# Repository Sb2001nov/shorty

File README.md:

# **Shorty (Re-Programable Macro Board)**

### you can fetch setup guide and files📂 [here](https://sb2001nov.github.io/shorty/)

## **Components Hardware Required:**

1. Raspberry pi Pico ([here](https://datasheets.raspberrypi.com/pico/pico-datasheet.pdf))
1. Cherry MX Style Switch’s ([here](https://cdn.sparkfun.com/datasheets/Components/Switches/MX%20Series.pdf))
1. General Purpose led ([here](https://learn.adafruit.com/all-about-leds/what-is-an-led))
1. Our PCB (here)

## **Specifications For Shorty:**

Contains 9 re-programmable keys for your macro, keys are laid out in 3x3 matrix.

1. **Switch:** Key switch with fixation pins (1 pole), hot swappable (should contain same mount point as mentioned).
1. **Keycaps:** can be 3d printed using given model or can pe purchased online.

### **Note:**
Match keycap size before purchasing, supported keycaps are alphabetic caps.

1. **Size:** x = 93.47mm, y = 62.99 mm
1. **Mounting:** Keycap can be mounted using 5 2.1 mm mounting bits.
1. **Connection:** Micro-B USB.

## **Programing Specification:**

1. micro-python - supported firmware and installation guide is [here](https://projects.raspberrypi.org/en/projects/getting-started-with-the-pico/3).
1. circuit-python - supported native and recommended to use.
1. C/C++ - can be uploaded using Thonny ide.
1. QMK firmware - customizable firmware.

## **Circuit Symantec**

Each switch is connected to a 3.3-Volt power pin and the other pin is connected to a GPIO pin to receive the data from the switch(input).
It also contains an LED connected with a resistor which you can use to show the status of anything you desire like showing if the circuit is receiving voltage. 

Buttons are connected in such a way that each button has its own GPIO pin, **why?**
</br>
Because it contains only 9 switches and it would be useless to reduce the number of pin because it will increase the complexity on the connection and increase the number of components used, leading to the code complexity.

*Complete information about RP2040 can be found [here*](https://datasheets.raspberrypi.com/pico/pico-datasheet.pdf)*

## **PCB Symantec**

All the details about PCB can be found on the GitHub, just open the PCB folder in KiCad.

PCB can be printed by [JLCPCB](https://cart.jlcpcb.com/) just upload the Gerber zip file on JLCPCB website.

## **3d Renders for PCB and components**

### **CHERRY MX + KEYCAPS’**
Stander alphabetical keycap without any legends can be printed using translucent materials or solid material like PLA.

### **CHERRY MX SWITCH**
You can use any switch like blue, jade, etc. as long as you have same mounting point shown in the 3D model to be precise 1 pole without led Connections, with fixation point.

Details can be found [here](https://cdn.sparkfun.com/datasheets/Components/Switches/MX%20Series.pdf)

## **Additional use case:**
Can be use with the script included in “shorty.py” which help you to set keyboard shortcut in your device and then you can program your macro pad to send those specific commands to your device, this way you can swiftly change your macros.

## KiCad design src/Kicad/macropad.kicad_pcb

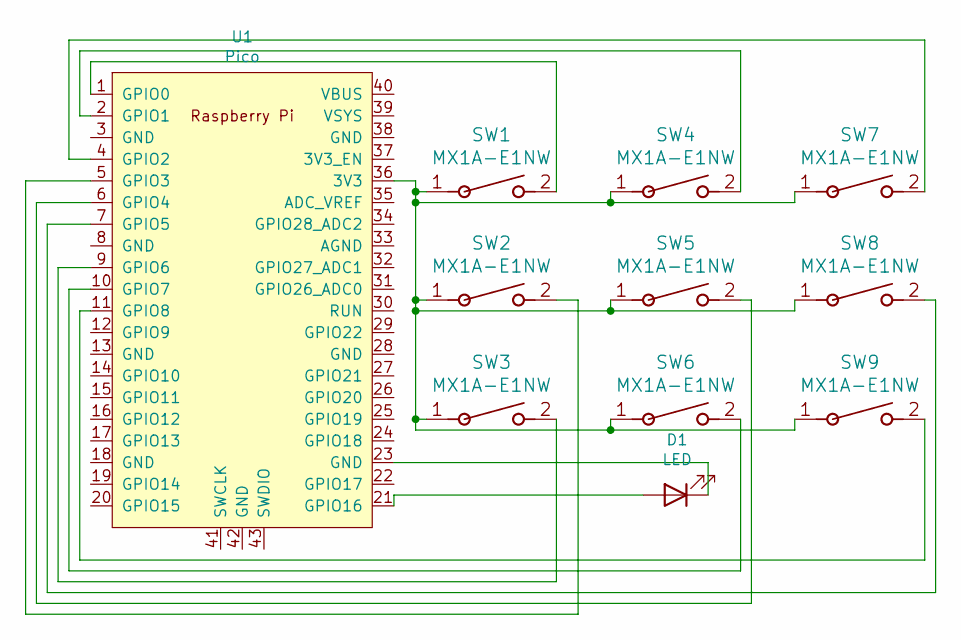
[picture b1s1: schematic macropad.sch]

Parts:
D1: LED; LED_D3.0mm
SW1, SW2, SW3, SW4, SW5, SW6, SW7, SW8, SW9: MX1A-E1NW; SW_Cherry_MX_1.00u_PCB
U1: Pico; RPi_Pico_SMD_TH

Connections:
unnamed: D1.1 (K), U1.23 (GND)
unnamed: D1.2 (A), U1.21 (GPIO16)
unnamed: SW1.1, SW2.1, SW3.1, SW4.1, SW5.1, SW6.1, SW7.1, SW8.1, SW9.1, U1.36 (3V3)
unnamed: SW1.2, U1.1 (GPIO0)
unnamed: SW2.2, U1.5 (GPIO3)
unnamed: SW3.2, U1.9 (GPIO6)
unnamed: SW4.2, U1.2 (GPIO1)
unnamed: SW5.2, U1.6 (GPIO4)
unnamed: SW6.2, U1.10 (GPIO7)
unnamed: SW7.2, U1.4 (GPIO2)
unnamed: SW8.2, U1.7 (GPIO5)
unnamed: SW9.2, U1.11 (GPIO8)

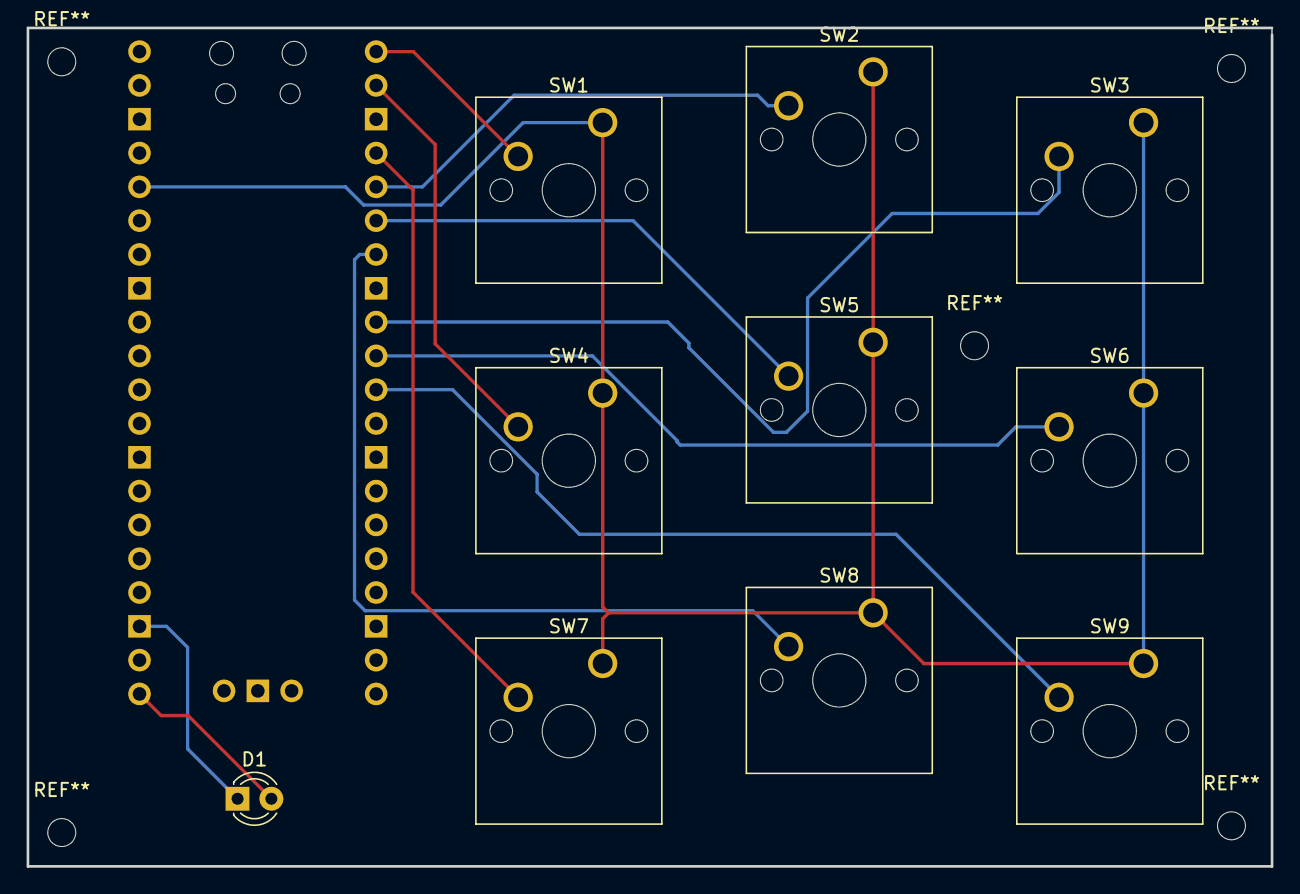
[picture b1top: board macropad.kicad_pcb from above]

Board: 2 copper layers, 93.5 x 63.0 mm, 11 parts (1 on the bottom side), 12 nets.

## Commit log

2021-12-07 base
    base structure
2021-12-08 Create cpp_example.ino
    c++ example
2021-12-08 not needed
2021-12-08 Set theme jekyll-theme-hacker
2021-12-08 backup
2021-12-08 Update micropython_example.py
    formatted
2021-12-08 typo
    wrong file name
2021-12-08 gerber
2021-12-09 readme
2021-12-09 Update README.md
    wrong file path
2021-12-09 Update README.md
    formated
2021-12-13 minor edit
2021-12-13 new img
2021-12-13 added_R
